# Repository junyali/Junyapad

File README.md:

# Junyapad

A custom 6-key macropad featuring per-key RGB LEDs (with some extras :p) a 128x32 0.91" OLD screen, a rotary encoder switch and a cool semi-open case design!

PCB designed in KiCAD, case built in OnShape, and firmware built using QMK. Pretty proud of this as it's fully independent (no assistance from friends needed or Q's asked :DD)

## Preview

| Description      | Image                          |
|------------------|--------------------------------|
| Schematic        |     |
| PCB              |           |
| PCB Render Front |  |
| PCB Render Back  |   |
| Case Render      |        |

## BOM

| Component                              | Footprint                                        | Qty | Unit Price (£) | Total Price (£) | Link                                                  |
|----------------------------------------|--------------------------------------------------|-----|----------------|-----------------|-------------------------------------------------------|
| SEEED XIAO RP2040                      | XIAO-RP2040-DIP                                  | 1   | 3.99           | 3.99            | https://www.aliexpress.com/item/1005004459618789.html |
| Cherry MX switches                     | N/A                                              | 6   | 0.21           | 1.26            | https://www.aliexpress.com/item/1005006255961111.html |
| Generic Keycaps                        | N/A                                              | 6   | 0.75           | 0.75            | https://www.aliexpress.com/item/1005005386897424.html |
| 1N4148 Diodes                          | D_DO-35_SOD27_P7.62mm_Horizontal                 | 6   | 0.02           | 0.12            | https://www.aliexpress.com/item/1005006245109375.html |
| SK6812 MINI LEDs                       | LED_SK6812MINI_PLCC4_3.5x3.5mm_P1.75mm           | 10  | 0.08           | 0.80            | https://www.aliexpress.com/item/1005001971988539.html |
| 128x32 0.91" OLED Display              | OLED_128x32                                      | 1   | 0.74           | 0.74            | https://www.aliexpress.com/item/1005008640132638.html |
| EC11 Rotary Encoder Switch             | RotaryEncoder_Alps_EC11E-Switch_Vertical_H20mm   | 1   | 0.74           | 0.74            | https://www.aliexpress.com/item/1005004907970664.html |
| 4.7kΩ Resistors                        | R_Axial_DIN0204_L3.6mm_D1.6mm_P7.62mm_Horizontal | 2   | 0.05           | 0.10            | https://www.aliexpress.com/item/1005006427040577.html |
| 0.1uF Disc Capacitors                  | C_Disc_D3.0mm_W1.6mm_P2.50mm                     | 10  | 0.01           | 0.10            | https://www.aliexpress.com/item/32973259342.html      |
| M3x16mm screws                         | N/A                                              | 4   | 0.04           | 0.16            | https://www.aliexpress.com/item/32844540184.html      |
| M3 hex nuts                            | N/A                                              | 4   | 0.03           | 0.12            | https://www.aliexpress.com/item/1005007593861199.html |
| PCB Fabricated (JLCPCB, incl shipping) | N/A                                              | 5   | 0.94           | 4.70            | https://jlcpcb.com                                    |
| 3D Printed Case (#printing-legion)     | N/A                                              | 1   | 0.00           | 0.00            | https://printlegion.hackclub.com                      |

Total Price: **£13.58** (*approx US$18.54*)

*Prices are a bit wonky since most products must be bought in bulk - this is an optimistic BOM*

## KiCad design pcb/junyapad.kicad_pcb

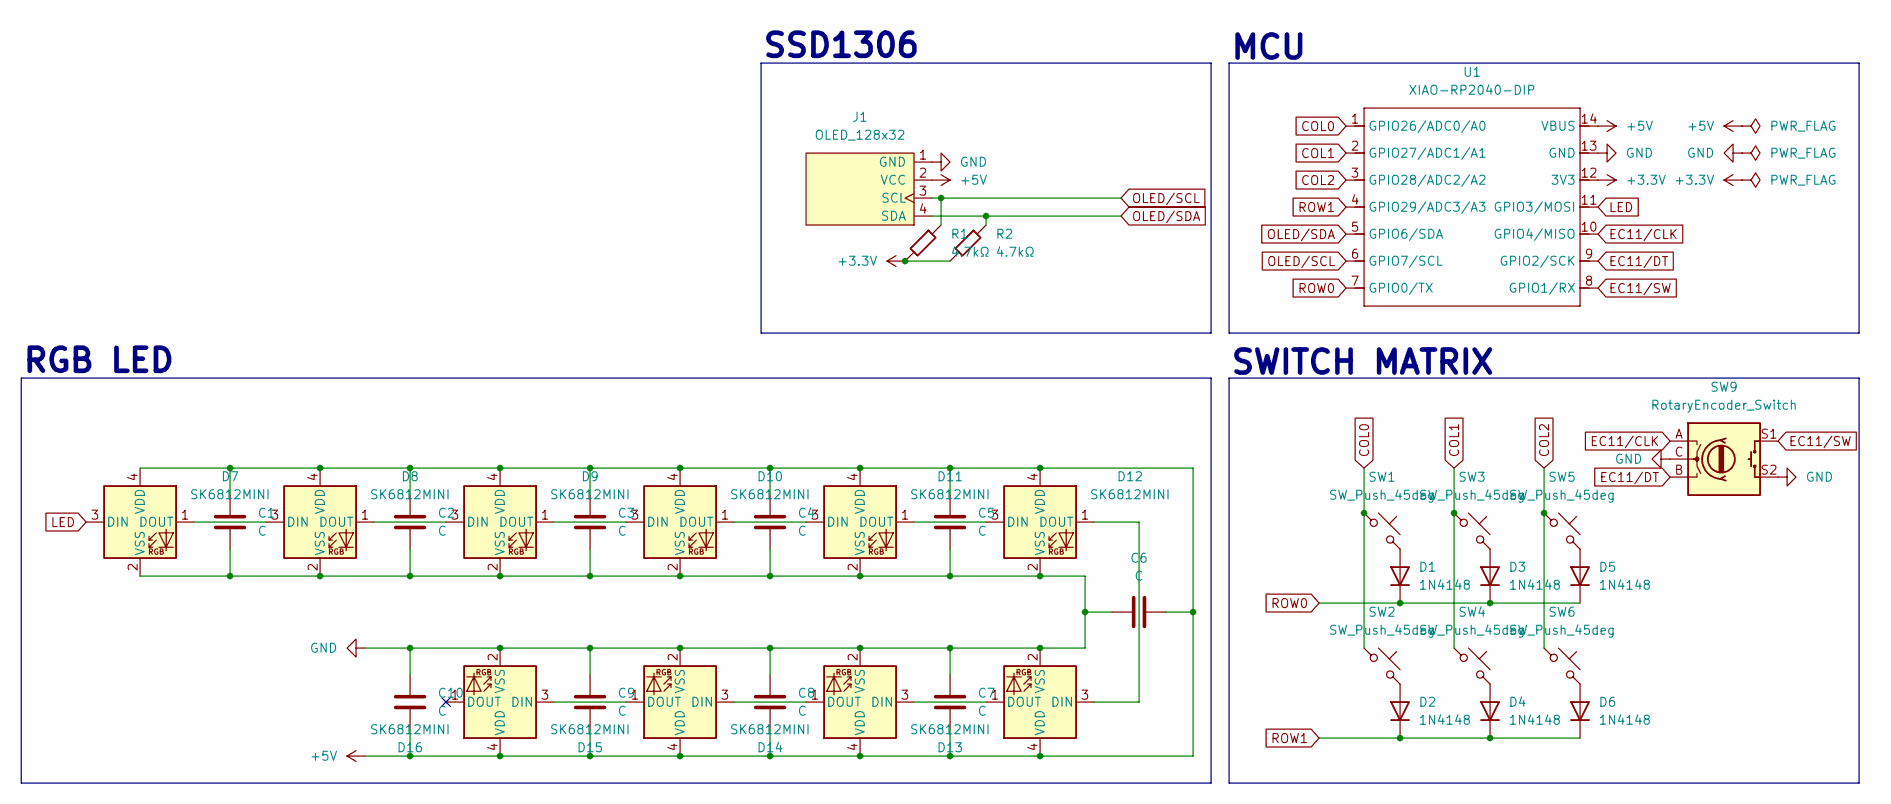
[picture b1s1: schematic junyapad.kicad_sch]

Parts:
C1, C2, C3, C4, C5, C6, C7, C8, C9, C10: C; C_Disc_D3.0mm_W1.6mm_P2.50mm
D1, D2, D3, D4, D5, D6: 1N4148; D_DO-35_SOD27_P7.62mm_Horizontal
D7, D8, D9, D10, D11, D12, D13, D14, D15, D16: SK6812MINI; LED_SK6812MINI_PLCC4_3.5x3.5mm_P1.75mm
J1: OLED_128x32
R1, R2: 4.7kΩ; R_Axial_DIN0204_L3.6mm_D1.6mm_P7.62mm_Horizontal
SW1, SW2, SW3, SW4, SW5, SW6: SW_Push_45deg; MX-Solderable-1U
SW9: RotaryEncoder_Switch; RotaryEncoder_Alps_EC11E-Switch_Vertical_H20mm
U1: XIAO-RP2040-DIP

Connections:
+3.3V: R1.2, R2.2, U1.12 (3V3)
+5V: C1.1, C2.1, C3.1, C4.1, C5.1, C6.2, C7.2, C8.2, C9.2, C10.2, D7.4 (VDD), D8.4 (VDD), D9.4 (VDD), D10.4 (VDD), D11.4 (VDD), D12.4 (VDD), D13.4 (VDD), D14.4 (VDD), D15.4 (VDD), D16.4 (VDD), J1.2 (VCC), U1.14 (VBUS)
COL0: SW1.1, SW2.1, U1.1 (GPIO26/ADC0/A0)
COL1: SW3.1, SW4.1, U1.2 (GPIO27/ADC1/A1)
COL2: SW5.1, SW6.1, U1.3 (GPIO28/ADC2/A2)
EC11/CLK: SW9.A, U1.10 (GPIO4/MISO)
EC11/DT: SW9.B, U1.9 (GPIO2/SCK)
EC11/SW: SW9.S1, U1.8 (GPIO1/RX)
GND: C1.2, C2.2, C3.2, C4.2, C5.2, C6.1, C7.1, C8.1, C9.1, C10.1, D7.2 (VSS), D8.2 (VSS), D9.2 (VSS), D10.2 (VSS), D11.2 (VSS), D12.2 (VSS), D13.2 (VSS), D14.2 (VSS), D15.2 (VSS), D16.2 (VSS), J1.1 (GND), SW9.C, SW9.S2, U1.13 (GND)
LED: D7.3 (DIN), U1.11 (GPIO3/MOSI)
unnamed: D1.2 (A), SW1.2
unnamed: D2.2 (A), SW2.2
unnamed: D3.2 (A), SW3.2
unnamed: D4.2 (A), SW4.2
unnamed: D5.2 (A), SW5.2
unnamed: D6.2 (A), SW6.2
unnamed: D7.1 (DOUT), D8.3 (DIN)
unnamed: D8.1 (DOUT), D9.3 (DIN)
unnamed: D9.1 (DOUT), D10.3 (DIN)
unnamed: D10.1 (DOUT), D11.3 (DIN)
unnamed: D11.1 (DOUT), D12.3 (DIN)
unnamed: D12.1 (DOUT), D13.3 (DIN)
unnamed: D13.1 (DOUT), D14.3 (DIN)
unnamed: D14.1 (DOUT), D15.3 (DIN)
unnamed: D15.1 (DOUT), D16.3 (DIN)
OLED/SCL: J1.3 (SCL), R1.1, U1.6 (GPIO7/SCL)
OLED/SDA: J1.4 (SDA), R2.1, U1.5 (GPIO6/SDA)
ROW0: D1.1 (K), D3.1 (K), D5.1 (K), U1.7 (GPIO0/TX)
ROW1: D2.1 (K), D4.1 (K), D6.1 (K), U1.4 (GPIO29/ADC3/A3)

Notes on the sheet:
SSD1306
SWITCH MATRIX
RGB LED
MCU

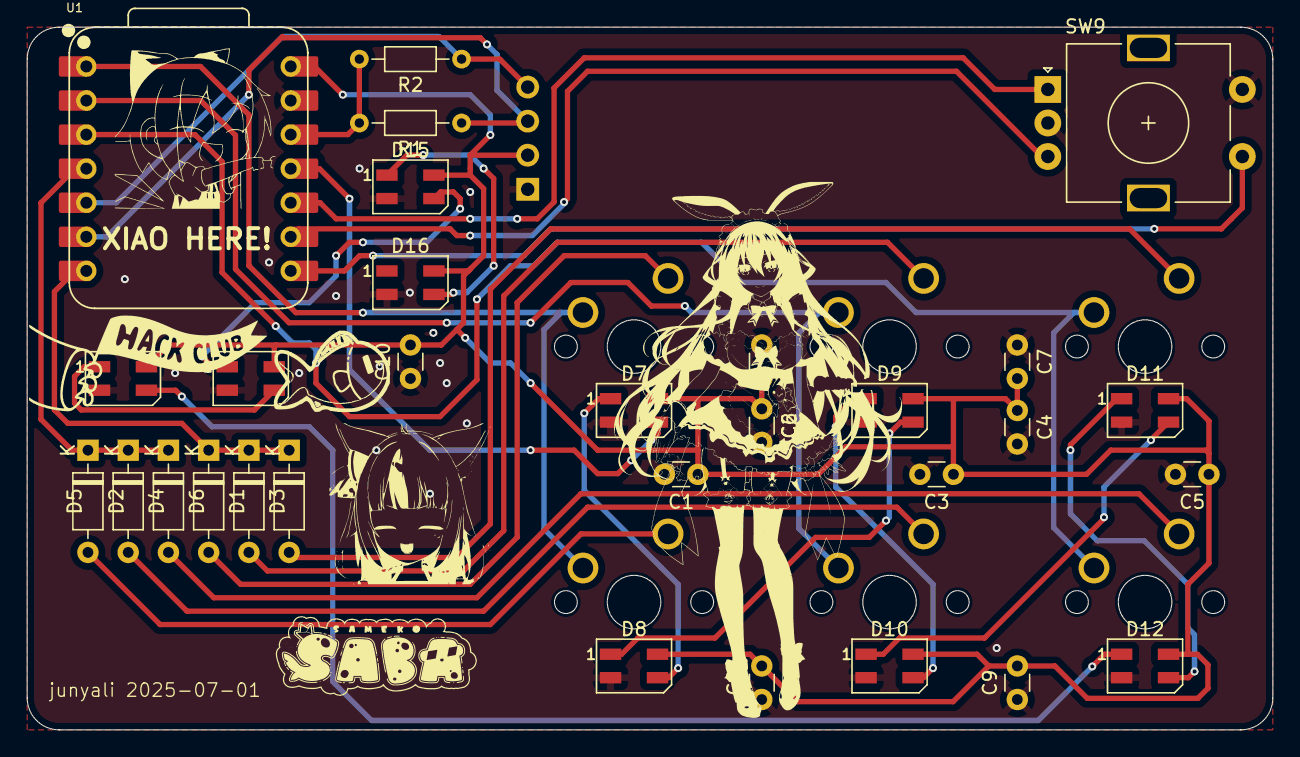
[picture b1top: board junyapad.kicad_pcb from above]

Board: 2 copper layers, 92.9 x 52.4 mm, 37 parts (0 on the bottom side), 29 nets.

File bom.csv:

"Id";"Designator";"Footprint";"Quantity";"Designation";"Supplier and ref";
1;"D3,D6,D4,D1,D2,D5";"D_DO-35_SOD27_P7.62mm_Horizontal";6;"1N4148";;;
2;"D10,D14,D8,D15,D9,D11,D12,D13,D7,D16";"LED_SK6812MINI_PLCC4_3.5x3.5mm_P1.75mm";10;"SK6812MINI";;;
3;"C10,C8,C2,C5,C7,C4,C6,C1,C3,C9";"C_Disc_D3.0mm_W1.6mm_P2.50mm";10;"C";;;
4;"R1,R2";"R_Axial_DIN0204_L3.6mm_D1.6mm_P7.62mm_Horizontal";2;"4.7kΩ";;;
5;"SW1,SW2,SW4,SW6,SW3,SW5";"MX-Solderable-1U";6;"SW_Push_45deg";;;
6;"J1";"OLED_128x32";1;"OLED_128x32";;;
7;"SW9";"RotaryEncoder_Alps_EC11E-Switch_Vertical_H20mm";1;"RotaryEncoder_Switch";;;
8;"U1";"XIAO-RP2040-DIP";1;"XIAO-RP2040-DIP";;;

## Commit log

2025-07-01 Add required libraries
2025-07-01 Import libraries into KiCAD
2025-07-01 Setup KiCAD Project
2025-07-01 Add MX_V2 library
2025-07-01 Update schematic
2025-07-01 Layout PCB
2025-07-01 Rearrange Capacitors
2025-07-01 Update PCB
2025-07-01 Add missing 3d model
2025-07-02 Export CAD files
2025-07-02 Generate gerbers.zip
2025-07-02 Add and build QMK firmware
2025-07-02 Add README.md
2025-07-02 Add bom.csv
2025-07-03 Fix BOM
2025-07-04 Fix wonky maths
2025-07-04 Add USD total
